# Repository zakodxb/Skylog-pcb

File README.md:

# Skylog-pcb
This is a PCB Im making for my rc plane and rocket! It will track velocity, distance, time, acceleration, gps, have a buzzer and a servo module to release a parachute on apogee!!

I created this for my school club as well, where we test out rc planes and would love to add this addition and teach the cub how to make a pcb. 

I first started with an idea and a name sky logger. I'v always thought about creating pcbs but thought they were to intercate and difficult. I learned that the best way to learn is to do, so instead of watching a youtube video I went right into it, were I succesfully created this amazing pcb, my first ever. I first started with a list of parts that I will probably use. This consisted of a gps, buzzer, led, distance and velocity tracker, esp32 Pico and more. 

## Schmatic 

After grabbing my list of modules that will be useful and that I will need. Then I started placing them, not worrying about connections till after. I changed the pin name and direction and power type, as well as changing my list of materials as I continued. I wired it all up to the espc 32 signal wires as well as connecting all the gnd to gnd. I then also made my VCC 5.5vb connect to the other 5.5v same with 3v

## PCB !!!!

After I set my footpringts and got ran ERC to make sure all the connections were right and that they were no errors, I started on my PCB. First I started by creating a rectangular area to put my all my modules in, after I did that, I looked at the ghost lines and tried my best to put the modules in the best postioton so that's its the most direct way and least complicated way to wire. I stared wiring modules together, but then ran into an issue. No matter what I tried, I could not connect the gnd all to together, after about an hour or so I went to do some research and found out I can just make a whole copper layer just for the GND which helped so much and made the wiring a lot less messier. I also had to take into account the fact that the modules as well take place, so I make sure to give each pin module a good distance away from each other to make sure everything fits. After wiring everything and making sure they were no errors with the DRC, I started with the PCB art. For this, I used Claude AI which gave me some really good generative designs for the backpalte. All I did was input these into Ki KAD and it looked amazing. I did one last check of DRC, wiring, the 3d model to make sure that nothing was wrong before uploading the files

## Cost (AliExpress order)

For the materials, I did my best to go the cheapest route (AliExpress) and spent alot of time to find some cheap but good modules. There are alot of bulk packs because They usualy sell really cheap parts in bulk of 20-50 and you cant just buy your exact amount. I checked with PCB fabricators in the UAE but was not able to receive an email back or find a price. I sellted on JLCBWAY, which is onyl around 24 USD with shipping, as you get a 10 dollar ish discount first time. I chose the cheapest shipping as well, and its suppose to come in 1-2 weeks of ordering.
| Name | Quantity | Unit Price (USD) | Total (USD) | Price (AED) | Link | Notes |
|---|---:|---:|---:|---:|---|---|
| Raspberry Pi Pico (RP2040, with headers) | 1 | 16.17 | 16.17 | 59.38 | [AliExpress](https://www.aliexpress.com/item/1005008058623788.html) | Main controller (A1) |
| GPS module GY-NEO6MV2 | 1 | 12.62 | 12.62 | 46.34 | [AliExpress](https://www.aliexpress.com/item/1005006153090346.html) | Position logging, plane only |
| W25Q64JVSSIQ SPI flash, SOIC-8 | 1 | 6.73 | 6.73 | 24.71 | [AliExpress](https://www.aliexpress.com/item/1005011573616561.html) | Flight data storage (U1); pack of 5 |
| Active buzzer TMB12A | 1 | 2.54 | 2.54 | 9.31 | [AliExpress](https://www.aliexpress.com/item/1005013110978481.html) | Recovery beeper (via Q1); pack of 10 |
| 1N5819HW Schottky diode, SOD-123 | 1 | 2.49 | 2.49 | 9.16 | [AliExpress](https://www.aliexpress.com/item/1005009499190440.html) | Power protection (D1); pack of 50 |
| Ceramic capacitor 100nF | 1 | 2.71 | 2.71 | 9.96 | [AliExpress](https://www.aliexpress.com/item/1005011747293156.html) | Decoupling (C2, C3); pack of 100 |
| Electrolytic capacitor 100uF | 1 | 2.02 | 2.02 | 7.42 | [AliExpress](https://www.aliexpress.com/item/1005011811368397.html) | Power smoothing (C1) |
| 2N7002 MOSFET, SOT-23 | 1 | 2.18 | 2.18 | 8.01 | [AliExpress](https://www.aliexpress.com/item/1005010446312149.html) | Buzzer switch (Q1); pack of 50 |
| SS12D00G4 slide switch | 1 | 2.32 | 2.32 | 8.52 | [AliExpress](https://www.aliexpress.com/item/1005012453860112.html) | Power switch (SW1); pack of 20 |
| BMP280 pressure sensor module 3.3V | 1 | 1.98 | 1.98 | 7.26 | [AliExpress](https://www.aliexpress.com/item/1005007306812689.html) | Altitude (J1) |
| GY-521 MPU6050 IMU module | 1 | 1.75 | 1.75 | 6.43 | [AliExpress](https://www.aliexpress.com/item/1005007989748804.html) | Motion sensing (J3) |
| Female pin header 2.54mm 1x__ | 1 | 2.19 | 2.19 | 8.06 | [AliExpress](https://www.aliexpress.com/item/1005012352493805.html) | Sensor and module sockets; pack of 10 |
| Female pin header 2.54mm 1x__ | 1 | 1.13 | 1.13 | 4.16 | [AliExpress](https://www.aliexpress.com/item/1005012352493805.html) | Sensor and module sockets; pack of 10 |
| Female pin header 2.54mm 1x__ | 1 | 2.14 | 2.14 | 7.85 | [AliExpress](https://www.aliexpress.com/item/1005012352493805.html) | Sensor and module sockets; pack of 10 |
| Female pin header 2.54mm 1x20 | 1 | 1.51 | 1.51 | 5.56 | [AliExpress](https://www.aliexpress.com/item/1005012940352449.html) | Pico sockets (A1); pack of 10 |
| Jumper shunt 2.54mm | 1 | 1.32 | 1.32 | 4.84 | [AliExpress](https://www.aliexpress.com/item/1005010500957186.html) | Mode jumper (J7); pack of 100 |
| Shipping | 1 | 6.74 | 6.74 | 24.77 |  | AliExpress shipping |
| Other (tax / fees) | 1 | 0.27 | 0.27 | 0.98 |  | Difference to order total |

   Full BOM with prices: [bom/bom.csv](Bom/bom.csv)

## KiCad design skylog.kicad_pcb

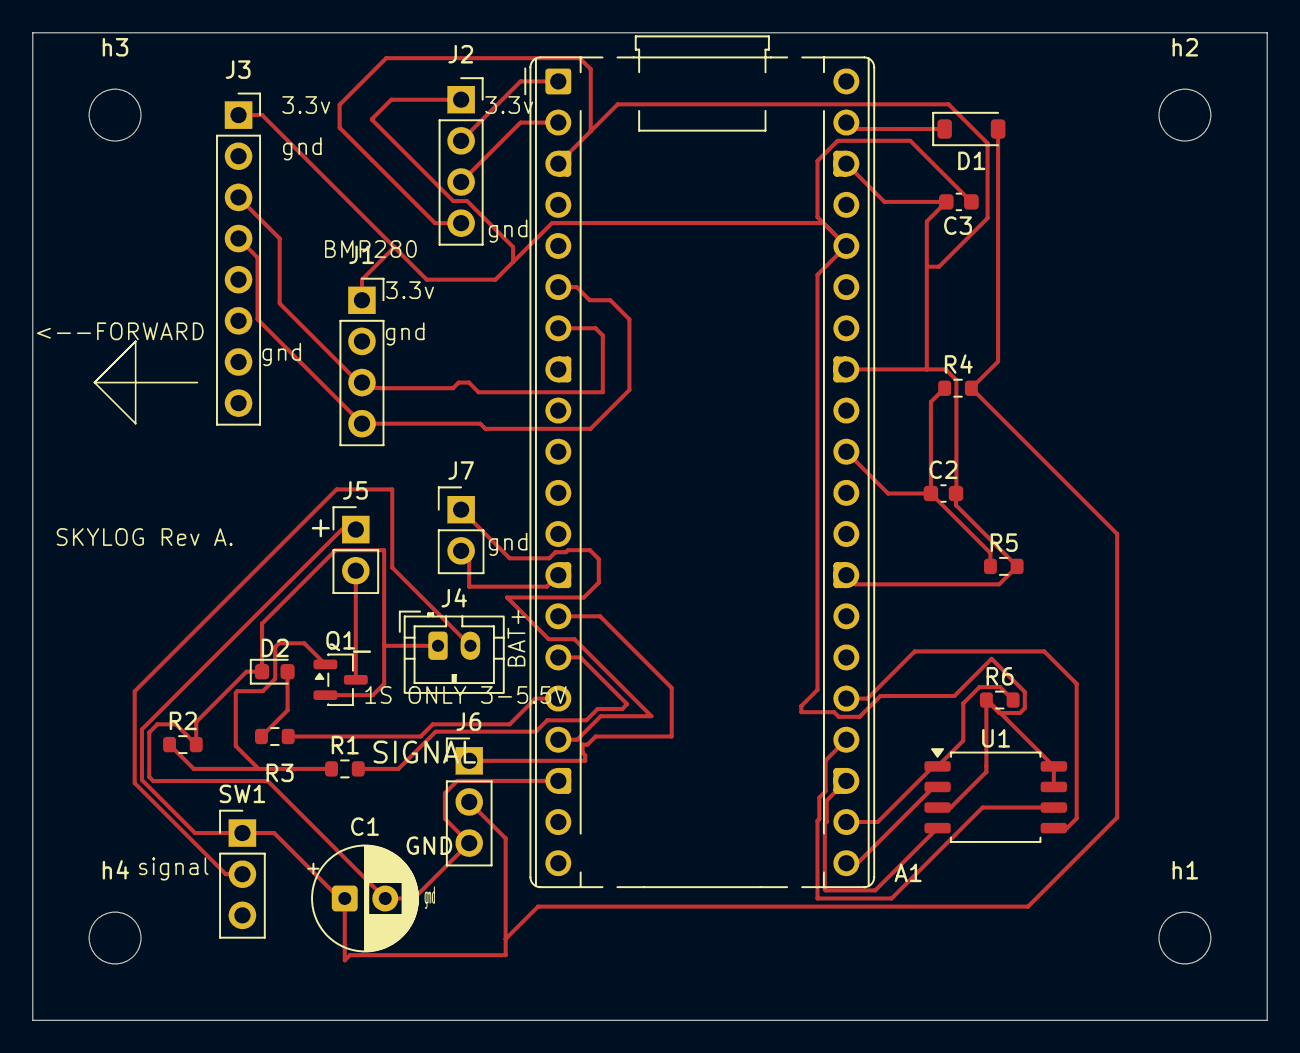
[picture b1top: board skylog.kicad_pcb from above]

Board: 2 copper layers, 76.2 x 61.0 mm, 26 parts (0 on the bottom side), 21 nets.

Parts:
A1: RaspberryPi_Pico; RaspberryPi_Pico_Common_THT
C1: C_Polarized; CP_Radial_D6.3mm_P2.50mm
C2, C3: 100nf; C_0603_1608Metric
D1: D_Schottky; D_SOD-123
D2: LED; LED_0603_1608Metric
J1: bmp280; PinSocket_1x04_P2.54mm_Vertical
J2: GPS; PinSocket_1x04_P2.54mm_Vertical
J3: MPU6050; PinSocket_1x08_P2.54mm_Vertical
J4: battery connector; JST_PH_B2B-PH-K_1x02_P2.00mm_Vertical
J5: buzzer header; PinHeader_1x02_P2.54mm_Vertical
J6: servo header; PinHeader_1x03_P2.54mm_Vertical
J7: mode jumper; PinHeader_1x02_P2.54mm_Vertical
Q1: 2N7002; SOT-23
R1: 100; R_0603_1608Metric
R2, R6: 10k; R_0603_1608Metric
R3: 330; R_0603_1608Metric
R4, R5: 100k; R_0603_1608Metric
SW1: SW_SPDT; PinHeader_1x03_P2.54mm_Vertical
U1: W25Q64JV; SOIC-8_5.3x5.3mm_P1.27mm
h1, h2, h3, h4: MountingHole_3.2mm_M3

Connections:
+3.3V: A1.36 (3V3), C3.2, J1.1 (vcc), J2.1 (vcc), J3.1 (vcc), R6.1, U1.3 (~WP/IO_{2}), U1.7 (~HOLD/~RESET/IO_{3}), U1.8 (VCC)
/vbat: C1.1, D1.2 (A), J5.1 (+), J6.2 (v+), R4.2, SW1.1 (A)
GND: A1.3 (GND), A1.8 (GND), A1.13 (GND), A1.18 (GND), A1.23 (GND), A1.28 (GND), A1.33 (AGND), A1.38 (GND), C1.2, C2.2, C3.1, D2.1 (K), J1.2 (gnd), J2.4 (gnd), J3.2 (gnd), J3.7 (ado), J4.1 (BAT_-), J6.3 (gnd), J7.2 (gnd), Q1.2 (S), R2.2, R5.2, U1.4 (GND)
unnamed: A1.1 (GPIO0), J2.2 (rx)
unnamed: A1.2 (GPIO1), J2.3 (tx)
unnamed: A1.6 (GPIO4), J1.4 (sda), J3.4 (sda)
unnamed: A1.7 (GPIO5), J1.3 (scl), J3.3 (scl)
unnamed: A1.14 (GPIO10), J6.1 (signal)
unnamed: A1.15 (GPIO11), R1.2
unnamed: A1.16 (GPIO12), R3.2
unnamed: A1.17 (GPIO13), J7.1 (mode)
unnamed: A1.21 (GPIO16), U1.2 (DO/IO_{1})
unnamed: A1.22 (GPIO17), R6.2, U1.1 (~CS)
unnamed: A1.24 (GPIO18), U1.6 (CLK)
unnamed: A1.25 (GPIO19), U1.5 (DI/IO_{0})
unnamed: A1.31 (GPIO26_ADC0), C2.1, R4.1, R5.1
unnamed: A1.39 (VSYS), D1.1 (K)
unnamed: D2.2 (A), R3.1
unnamed: J4.2 (BAT_+), SW1.2 (B)
unnamed: J5.2 (-), Q1.3 (D)
unnamed: Q1.1 (G), R1.1, R2.1
